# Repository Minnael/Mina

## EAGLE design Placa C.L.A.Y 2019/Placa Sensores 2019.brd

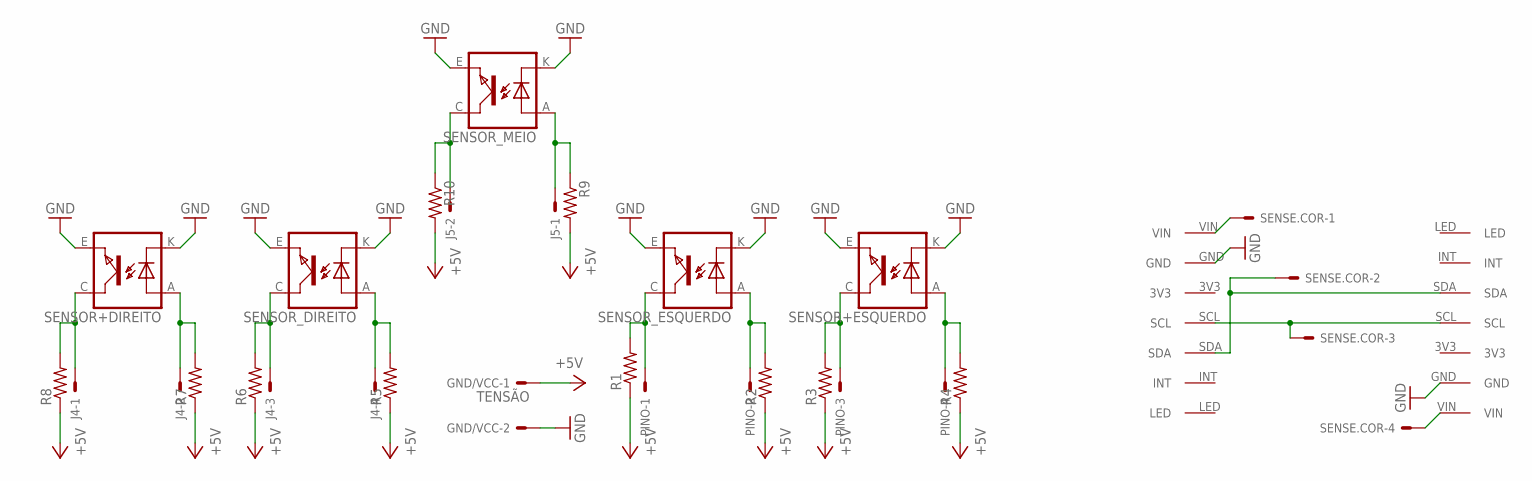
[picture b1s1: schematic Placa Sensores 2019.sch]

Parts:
GND/VCC: TENSÃO; 6410-02
J4: CONN_0427-2041; 6410-04
J5: CONN_0227-2021; 6410-02
PINO: CONN_0427-2041; 6410-04
R1, R2, R3, R4, R5, R6, R7, R8: R-US_0207/12; 0207/12
R9, R10: R-US_0204/7; 0204/7
SENSE.COR: CONN_0427-2041; 6410-04
SENSOR+DIREITO: TCRT5000
SENSOR+ESQUERDO: TCRT5000
SENSOR_DIREITO: TCRT5000
SENSOR_ESQUERDO: TCRT5000
SENSOR_MEIO: TCRT5000
TCS1, TCS2: TCS34725

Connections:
+5V: GND/VCC.1, R1.1, R2.1, R3.1, R4.1, R5.1, R6.1, R7.1, R8.1, R9.2, R10.2
GND: GND/VCC.2, SENSOR+DIREITO.E (EMITTER), SENSOR+DIREITO.K (CATHODE), SENSOR+ESQUERDO.E (EMITTER), SENSOR+ESQUERDO.K (CATHODE), SENSOR_DIREITO.E (EMITTER), SENSOR_DIREITO.K (CATHODE), SENSOR_ESQUERDO.E (EMITTER), SENSOR_ESQUERDO.K (CATHODE), SENSOR_MEIO.E (EMITTER), SENSOR_MEIO.K (CATHODE), TCS1.GND, TCS2.GND
unnamed: SENSE.COR.1, TCS1.VIN
unnamed: SENSE.COR.2, TCS1.SDA, TCS2.SDA
unnamed: SENSE.COR.3, TCS1.SCL, TCS2.SCL
unnamed: SENSE.COR.4, TCS2.VIN
unnamed: PINO.3, R3.2, SENSOR+ESQUERDO.C (COLLECTOR)
unnamed: PINO.2, R2.2, SENSOR_ESQUERDO.A (ANODE)
unnamed: J4.4, R5.2, SENSOR_DIREITO.A (ANODE)
unnamed: PINO.4, R4.2, SENSOR+ESQUERDO.A (ANODE)
unnamed: PINO.1, R1.2, SENSOR_ESQUERDO.C (COLLECTOR)
unnamed: J5.2, R10.1, SENSOR_MEIO.C (COLLECTOR)
unnamed: J5.1, R9.1, SENSOR_MEIO.A (ANODE)
unnamed: J4.3, R6.2, SENSOR_DIREITO.C (COLLECTOR)
unnamed: J4.2, R7.2, SENSOR+DIREITO.A (ANODE)
unnamed: J4.1, R8.2, SENSOR+DIREITO.C (COLLECTOR)

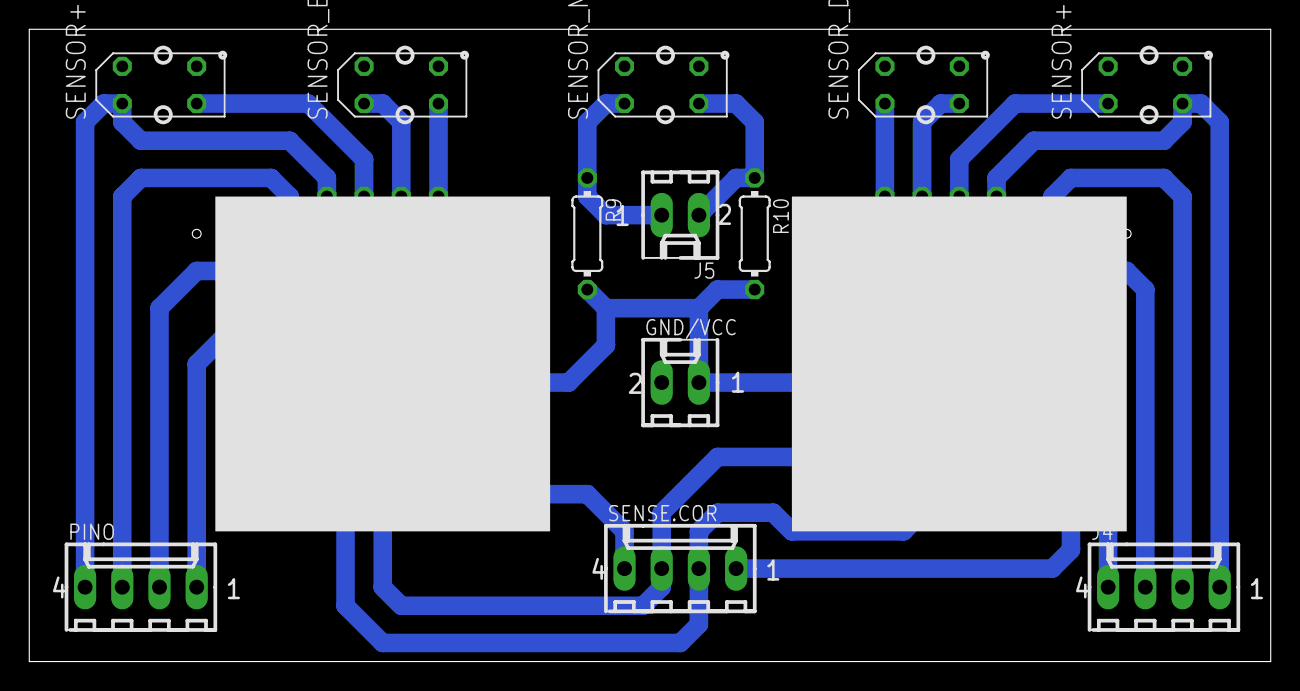
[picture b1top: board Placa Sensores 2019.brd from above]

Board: 2 copper layers, 84.8 x 43.2 mm, 22 parts (0 on the bottom side), 16 nets.

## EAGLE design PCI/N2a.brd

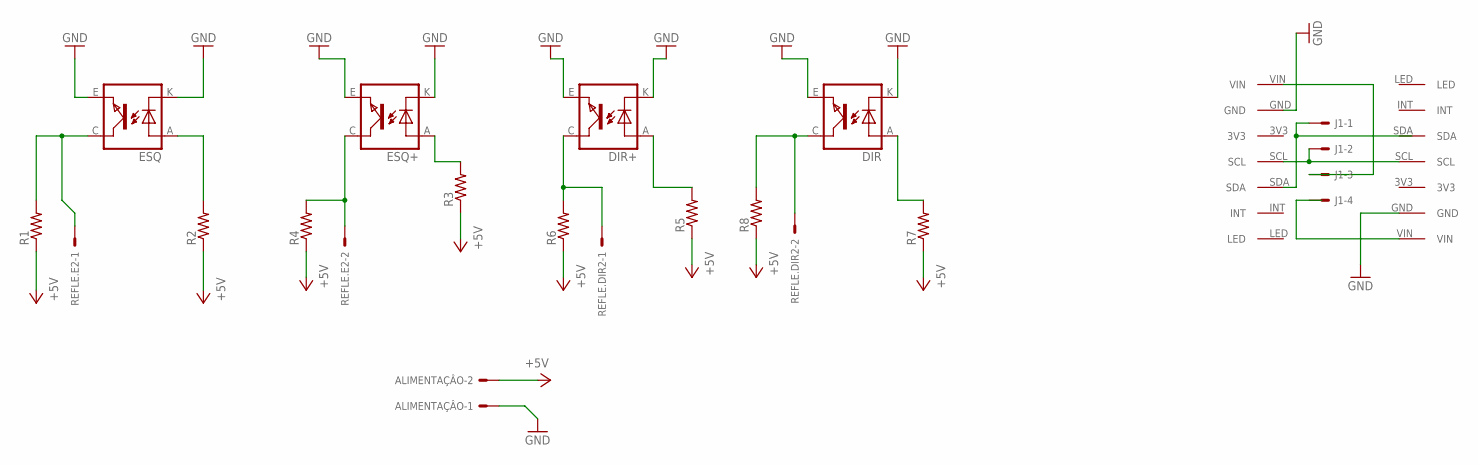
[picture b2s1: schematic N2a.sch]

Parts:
ALIMENTAÇÂO: CONN_0205-7028; 7395-02
DIR: TCRT5000
DIR+: TCRT5000
ESQ: TCRT5000
ESQ+: TCRT5000
J1: CONN_0405-7048; 7395-04
R1, R2, R3, R4, R5, R6, R7, R8: R-US_0204/7; 0204/7
REFLE.DIR2, REFLE.E2: CONN_0205-7028; 7395-02
TCS1, TCS2: TCS34725

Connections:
+5V: ALIMENTAÇÂO.2, R1.1, R2.1, R3.1, R4.1, R5.1, R6.1, R7.1, R8.1
GND: ALIMENTAÇÂO.1, DIR.E (EMITTER), DIR.K (CATHODE), DIR+.E (EMITTER), DIR+.K (CATHODE), ESQ.E (EMITTER), ESQ.K (CATHODE), ESQ+.E (EMITTER), ESQ+.K (CATHODE), TCS1.GND, TCS2.GND
unnamed: ESQ+.C (COLLECTOR), R4.2, REFLE.E2.2
unnamed: ESQ.C (COLLECTOR), R1.2, REFLE.E2.1
unnamed: ESQ+.A (ANODE), R3.2
unnamed: DIR+.A (ANODE), R5.2
unnamed: DIR+.C (COLLECTOR), R6.2, REFLE.DIR2.1
unnamed: DIR.A (ANODE), R7.2
unnamed: DIR.C (COLLECTOR), R8.2, REFLE.DIR2.2
unnamed: J1.1, TCS1.SDA
unnamed: ESQ.A (ANODE), R2.2
unnamed: J1.2, TCS1.SCL, TCS2.SCL
unnamed: J1.3, TCS1.VIN

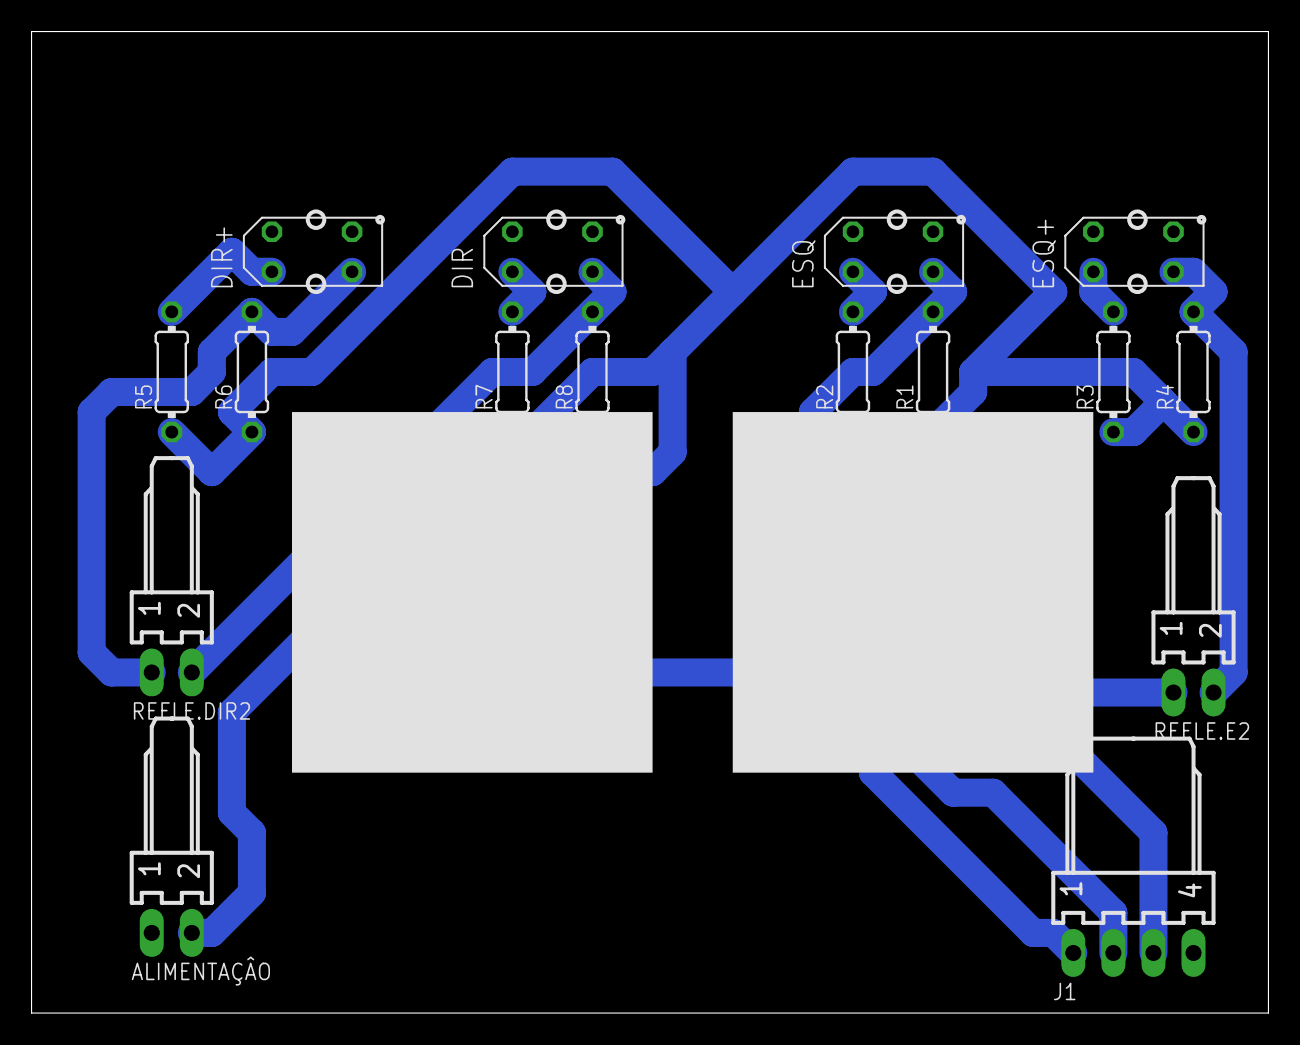
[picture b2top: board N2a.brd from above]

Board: 2 copper layers, 78.4 x 62.2 mm, 18 parts (0 on the bottom side), 13 nets.

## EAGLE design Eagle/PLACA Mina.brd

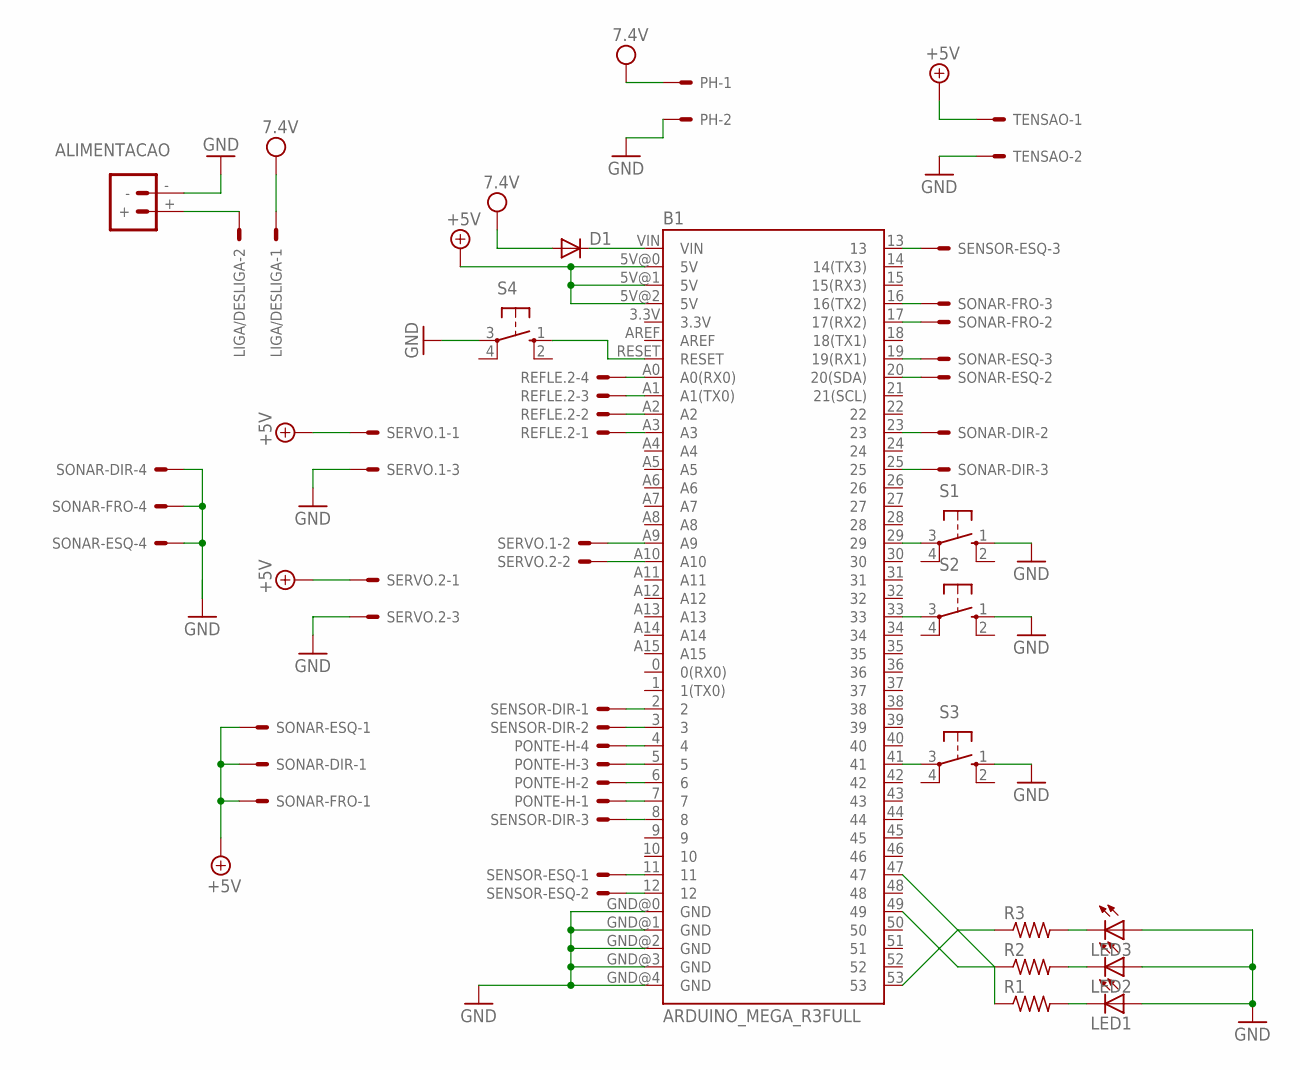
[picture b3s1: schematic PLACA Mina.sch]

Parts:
ALIMENTACAO: BATTERY_CONNXT60; XT60
B1: ARDUINO_MEGA_R3FULL; ARDUINO_MEGA
D1: 1N4004; DO41-10
LED1, LED2, LED3: LED5MM
LIGA/DESLIGA: CONN_0227-2021; 6410-02
PH: CONN_0227-2021; 6410-02
PONTE-H: CONN_0427-2041; 6410-04
R1, R2, R3: R-US_0204/7; 0204/7
REFLE.2: CONN_0427-2041; 6410-04
S1, S2, S3, S4: 10-XX; B3F-10XX
SENSOR-DIR: CONN_0327-2031; 6410-03
SENSOR-ESQ: CONN_0327-2031; 6410-03
SERVO.1, SERVO.2: CONN_0327-2031; 6410-03
SONAR-DIR: CONN_0427-2041; 6410-04
SONAR-ESQ: CONN_0427-2041; 6410-04
SONAR-FRO: CONN_0427-2041; 6410-04
TENSAO: CONN_0227-2021; 6410-02

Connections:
+5V: B1.5V@0 (5V), B1.5V@1 (5V), B1.5V@2 (5V), SERVO.1.1, SERVO.2.1, SONAR-DIR.1, SONAR-ESQ.1, SONAR-FRO.1, TENSAO.1
GND: ALIMENTACAO.-, B1.GND@0 (GND), B1.GND@1 (GND), B1.GND@2 (GND), B1.GND@3 (GND), B1.GND@4 (GND), LED1.A, LED2.A, LED3.A, PH.2, S1.1 (S), S2.1 (S), S3.1 (S), S4.3, SERVO.1.3, SERVO.2.3, SONAR-DIR.4, SONAR-ESQ.4, SONAR-FRO.4, TENSAO.2
unnamed: B1.A3, REFLE.2.1
unnamed: B1.A2, REFLE.2.2
unnamed: B1.A1 (A1(TX0)), REFLE.2.3
unnamed: B1.A0 (A0(RX0)), REFLE.2.4
unnamed: B1.16 (16(TX2)), SONAR-FRO.3
unnamed: B1.17 (17(RX2)), SONAR-FRO.2
unnamed: B1.7, PONTE-H.1
unnamed: B1.6, PONTE-H.2
unnamed: B1.5, PONTE-H.3
unnamed: B1.4, PONTE-H.4
unnamed: B1.20 (20(SDA)), SONAR-ESQ.2
unnamed: B1.19 (19(RX1)), SONAR-ESQ.3
unnamed: B1.23, SONAR-DIR.2
unnamed: B1.25, SONAR-DIR.3
unnamed: B1.11, SENSOR-ESQ.1
unnamed: B1.12, SENSOR-ESQ.2
unnamed: B1.13, SENSOR-ESQ.3
unnamed: B1.2, SENSOR-DIR.1
unnamed: B1.3, SENSOR-DIR.2
unnamed: B1.8, SENSOR-DIR.3
unnamed: B1.A10, SERVO.2.2
unnamed: B1.A9, SERVO.1.2
unnamed: B1.29, S1.3
unnamed: B1.33, S2.3
unnamed: B1.41, S3.3
unnamed: B1.53, R3.1
unnamed: B1.49, R2.1
unnamed: B1.47, R1.1
unnamed: LED1.K (C), R1.2
unnamed: LED2.K (C), R2.2
unnamed: LED3.K (C), R3.2
unnamed: B1.VIN, D1.C
unnamed: ALIMENTACAO.+, LIGA/DESLIGA.2
unnamed: B1.RESET, S4.1 (S)
VDD: D1.A, LIGA/DESLIGA.1, PH.1

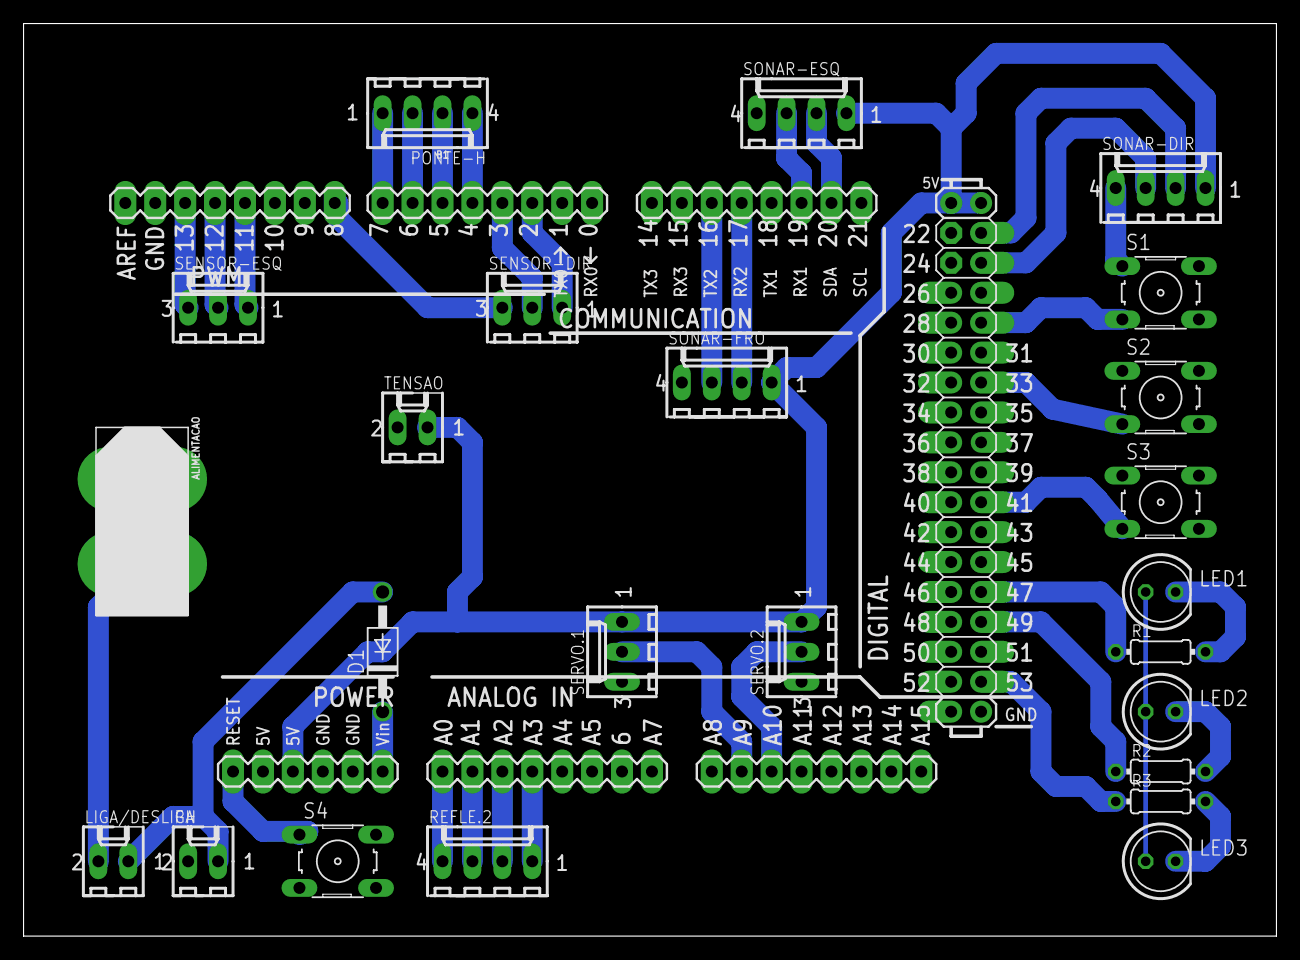
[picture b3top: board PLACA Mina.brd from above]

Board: 2 copper layers, 106.3 x 77.5 mm, 25 parts (0 on the bottom side), 37 nets.

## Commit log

2019-03-23 Exclusão de teste
2019-03-23 Adição de código (estrategia) + placas + chassi + etc.
2019-03-23 Organização de pastas.
2019-03-23 Pequena exclusão de arquviso repetidos.
2019-03-23 Organização de pastas 2.
2019-03-26 Adição de novas funções. Linha/Obs/Movimentos
2019-03-26 ++Es++OBS
2019-03-27 desintegração de classe propia da sala3
2019-03-27 ant __
2019-03-27 Mudançãs no metodo da sala3
2019-03-27 Retirada da classe sala3 && adição/mudança do metodo sala3 na classe estrategia(mãe).
2019-03-29 Adição de nova classe sala 3, mudanças de altissimo nivel na classe sala3 e no metodo sala3 da classe estrategia.
2019-03-29 Adição da classe sala3
2019-03-31 Placa C.L.A.Y 2019
2019-04-02 Adição de objetos + renovação da sala3
2019-04-03 Adições básicas na class sala3
2019-04-03 Troca de placa de sensores, que resultou na mudança da estrategia de seguir linha + pequenas mudanças na class sala3/movimento.
2019-04-04 Alteração na class movimento, o que fez melhorar o desempenho na rampa + alteração basicas no seguir linha.
2019-04-04 ++anterior
2019-04-05 Alteração na class sala3 (resgate.1).
2019-04-05 Obs++ (obs2.)
2019-04-05 Configuracao em delays e adicao de variaveis no obs.
2019-04-09 Pequenas atualizações no metódo OBS + mudanças de delay na class sala3.
2019-04-10 ALL ++
2019-04-11 Mudanças para a implementação do 5° sensor.
2019-04-13 Atualização na classe seguir linha e sensores.
2019-04-16 +ALL
